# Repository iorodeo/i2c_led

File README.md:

# IO Rodeo i2c_led 

Hardware design for IO Rodeo's i2c_led (in development).

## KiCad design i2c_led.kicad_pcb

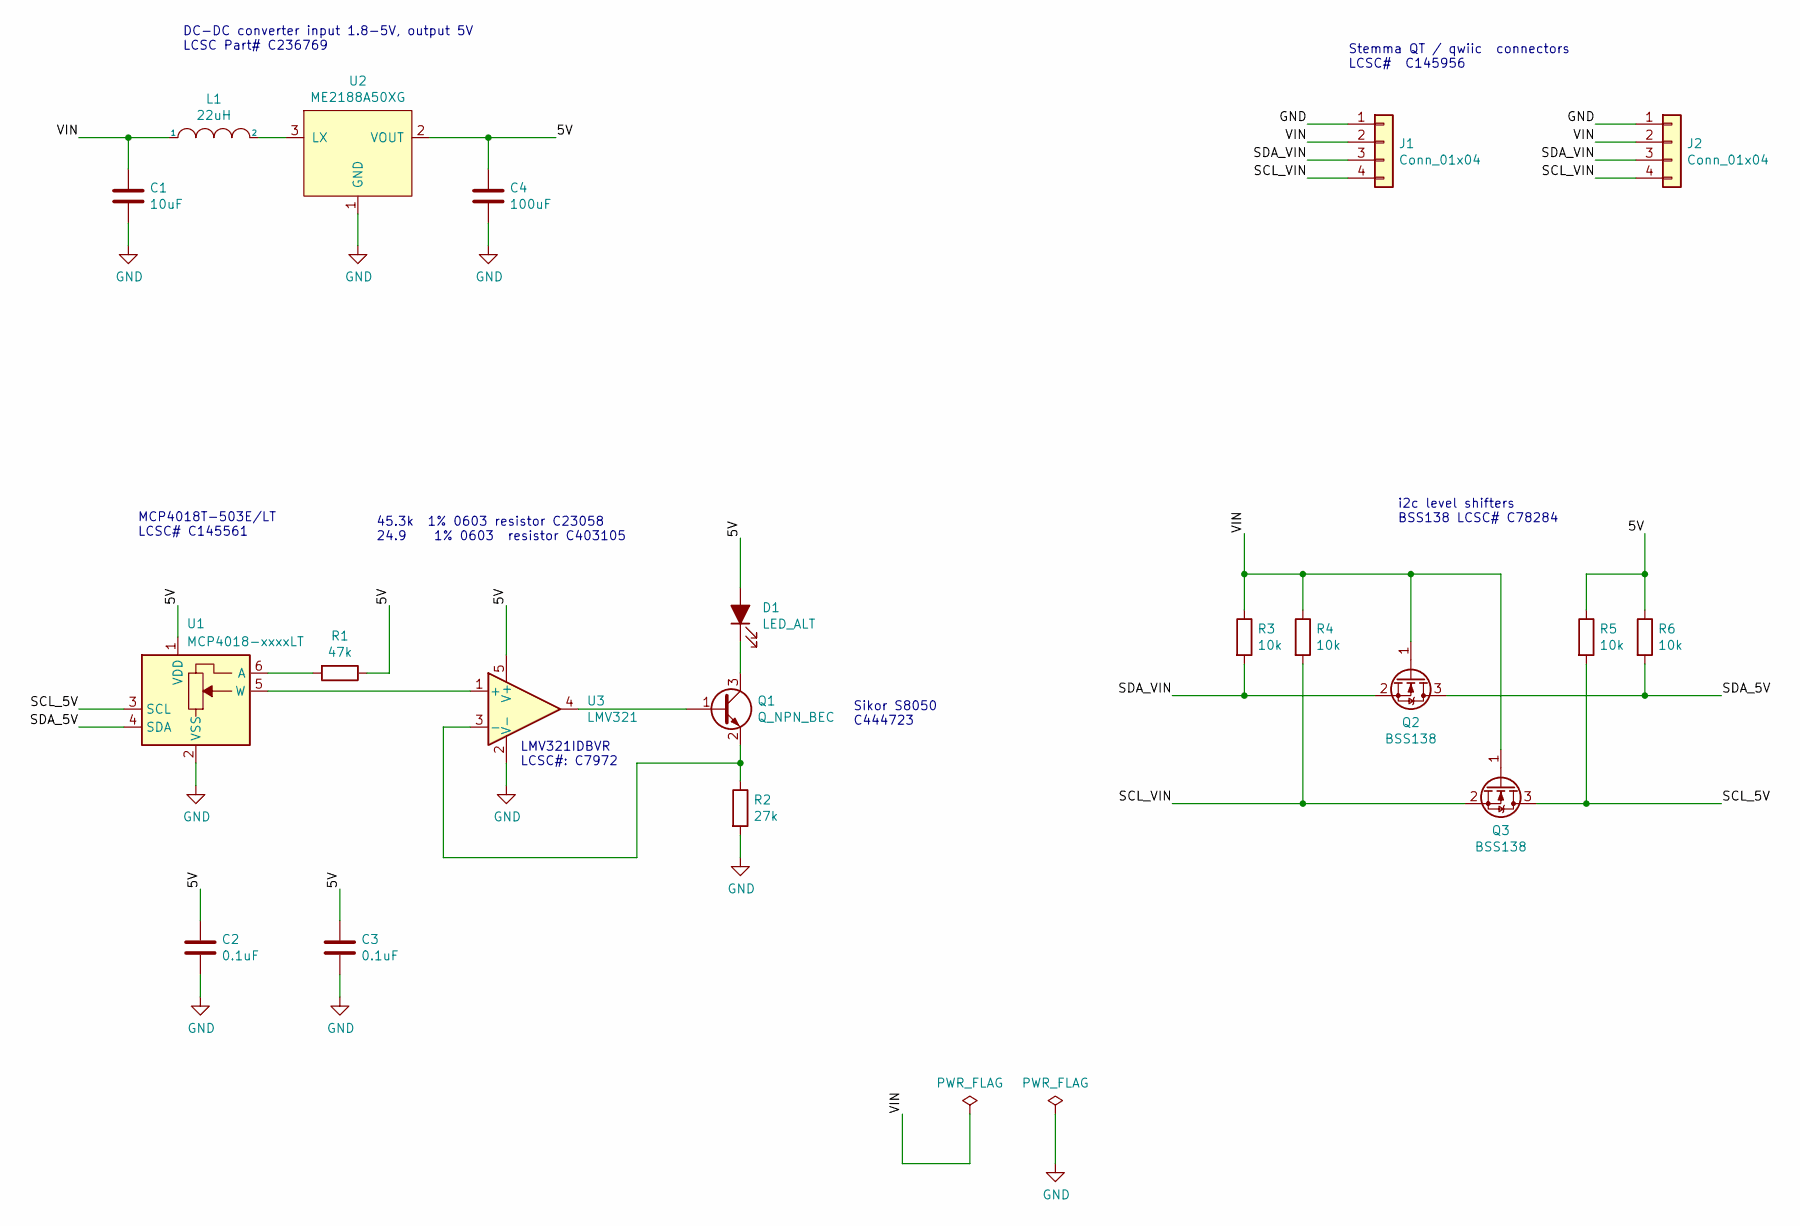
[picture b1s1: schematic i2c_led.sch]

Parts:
C1: 10uF; C_0402_1005Metric
C2, C3: 0.1uF; C_0402_1005Metric
C4: 100uF; C_0805_2012Metric
D1: LED_ALT; LED_0603_1608Metric
J1, J2: Conn_01x04; BOOMELE_SMD_SH_4PIN_RT
L1: 22uH; L_1206_3216Metric
Q1: Q_NPN_BEC; SOT-23
Q2, Q3: BSS138; SOT-23
R1: 47k; R_0402_1005Metric
R2: 27k; R_0402_1005Metric
R3, R4, R5, R6: 10k; R_0402_1005Metric
U1: MCP4018-xxxxLT; SOT-363_SC-70-6
U2: ME2188A50XG; SOT-23
U3: LMV321; SOT-23-5

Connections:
/5V: C2.1, C3.1, C4.1, D1.2 (A), R1.1, R5.1, R6.1, U1.1 (VDD), U2.2 (VOUT), U3.5 (V+)
/SCL_5V: Q3.3 (D), R5.2, U1.3 (SCL)
/SCL_VIN: J1.4, J2.4, Q3.2 (S), R4.2
/SDA_5V: Q2.3 (D), R6.2, U1.4 (SDA)
/SDA_VIN: J1.3, J2.3, Q2.2 (S), R3.2
/VIN: C1.1, J1.2, J2.2, L1.1, Q2.1 (G), Q3.1 (G), R3.1, R4.1
GND: C1.2, C2.2, C3.2, C4.2, J1.1, J2.1, R2.2, U1.2 (VSS), U2.1 (GND), U3.2 (V-)
unnamed: D1.1 (K), Q1.3 (C)
unnamed: L1.2, U2.3 (LX)
unnamed: Q1.1 (B), U3.4
unnamed: Q1.2 (E), R2.1, U3.3 (-)
unnamed: R1.2, U1.6 (A)
unnamed: U1.5 (W), U3.1 (+)

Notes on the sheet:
DC-DC converter input 1.8-5V, output 5V LCSC Part# C236769
Stemma QT / qwiic connectors LCSC# C145956
i2c level shifters BSS138 LCSC# C78284
MCP4018T-503E/LT LCSC# C145561
45.3k 1% 0603 resistor C23058 24.9 1% 0603 resistor C403105
LMV321IDBVR LCSC#: C7972
Sikor S8050 C444723

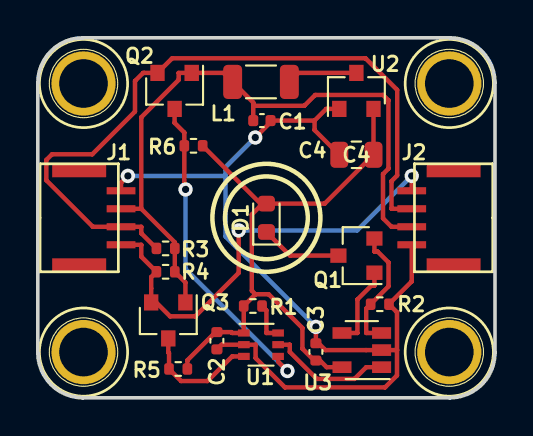
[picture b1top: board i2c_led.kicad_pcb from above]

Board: 2 copper layers, 25.4 x 20.0 mm, 24 parts (0 on the bottom side), 13 nets.

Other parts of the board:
M1, M2, M3, M4: MountingHole_2.5mm_Pad

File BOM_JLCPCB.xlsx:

Comment | Designator | Footprint | LCSC Part #（optional） | Qty
10uF ceramic capacitor | C1 | 0402 | C15525 | 1
0.1uF ceramic capacitor | C2, C3 | 0402 | C1525 | 2
100uF ceramic capacitor | C4 | 0805 | C141660 | 1
4-Pin Connector (BOOMELE) | J1 ,J2 | SMD,P=1mm | C145956 | 2
22uH Inductor | L1 | 1206 | C395020 | 1
NPN Bipolar Transistor | Q1 | SOT-23 | C444723 | 1
N-Channel MOSFET | Q2, Q3 | SOT-23 | C78284 | 2
resistor, 47k, 1% | R1 | 0402 | C25792 | 1
resistor, 27k, 1% | R2 | 0402 | C25771 | 1
resistor, 10k , 1% | R3, R4, R5, R6 | 0402 | C25744 | 4
Digital Potentiometers 5k | U1 | SC-70-6(SOT-363) | C145561 | 1
DC-DC Converters | U2 | SOT-23 | C236769 | 1
Op Amp LMV321 | U3 | SOT-23-5 | C7972 | 1
LED | D1 | 0603 | C375444 | 1

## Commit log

2021-10-25 Project creation.
2021-10-26 Worked on BOM.
2021-11-02 Work on BOM and footprint assignments.
2021-11-07 Worked on layout.
2021-11-07 Finished initial layout and routing.
2021-11-08 Resized board so that is above minimum required SMT assembly. Rerouted and remade gerbers and CPL file.
2021-11-08 Remade gerbers and CPL file once more after a few minor tweeks for manufacturing.
2021-11-09 Added notes.
2021-11-12 Added 3D design for 4-pin SH SMD connector.
2021-11-12 Added 3D render of PCB.
2022-01-01 Added notes about errors in design. Need to come back and fix them at some point.
